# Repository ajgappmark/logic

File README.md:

# logic
Programmable logic probe

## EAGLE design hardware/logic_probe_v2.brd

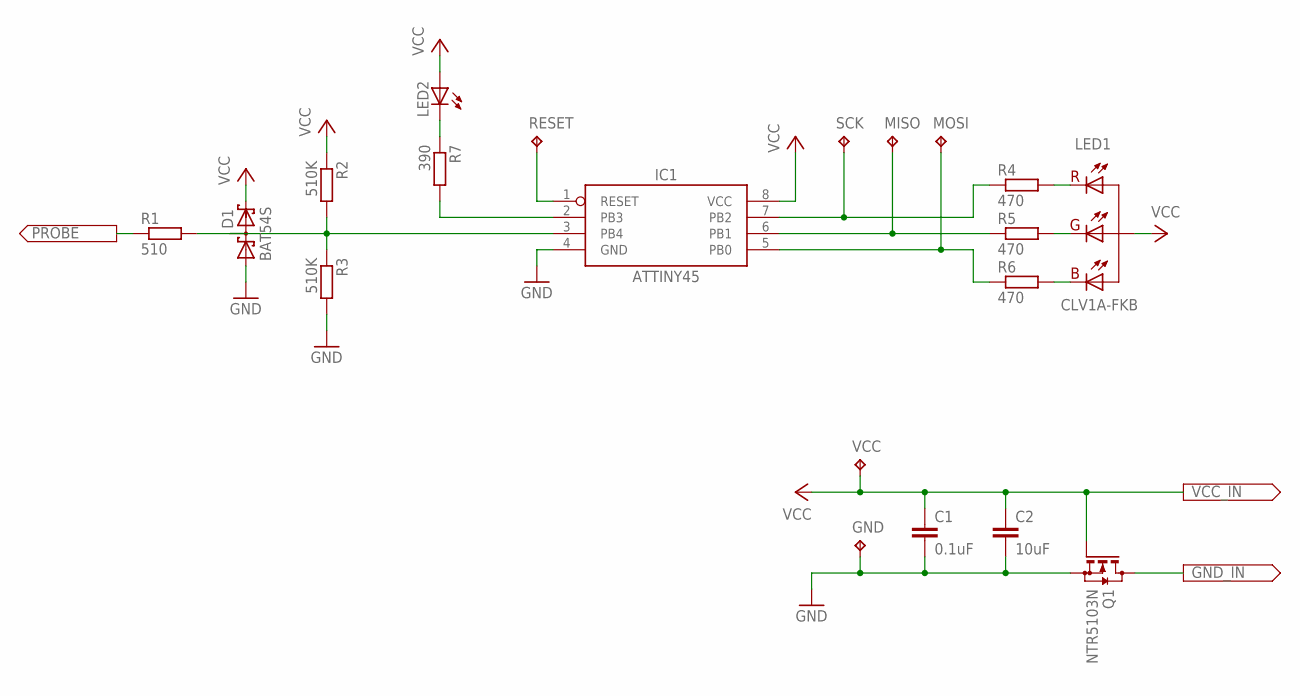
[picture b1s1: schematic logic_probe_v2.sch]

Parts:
C1: 0.1uF; C0805
C2: 10uF; C0805
D1: BAT54S; SOT23
GND: TPB1,27; B1,27
IC1: ATTINY45; TSSOP8
LED1: CLV1A-FKB; PLCC-4
LED2: LEDCHIPLED_0805; CHIPLED_0805
MISO: TPB1,27; B1,27
MOSI: TPB1,27; B1,27
Q1: NTR5103N; SOT23
R1: 510; R0805
R2, R3: 510K; R0805
R4, R5, R6: 470; R0805
R7: 390; R0805
RESET: TPB1,27; B1,27
SCK: TPB1,27; B1,27
VCC: TPB1,27; B1,27

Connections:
GND: C1.2, C2.2, D1.1 (A1), GND.TP, IC1.4 (GND), Q1.2 (S), R3.2
GND_IN: Q1.3 (D)
unnamed: LED1.1 (R), R4.2
unnamed: LED1.3 (G), R5.2
unnamed: LED1.4 (B), R6.2
unnamed: IC1.7 (PB2), R4.1, SCK.TP
unnamed: IC1.6 (PB1), MISO.TP, R5.1
unnamed: IC1.5 (PB0), MOSI.TP, R6.1
unnamed: IC1.2 (PB3), R7.2
unnamed: LED2.C, R7.1
unnamed: IC1.1 (RESET), RESET.TP
PROBE: R1.1
VCC: C1.1, C2.1, D1.2 (C2), IC1.8 (VCC), LED1.2 (CA), LED2.A, Q1.1 (G), R2.1, VCC.TP
VIN: D1.3 (C1A2), IC1.3 (PB4), R1.2, R2.2, R3.1

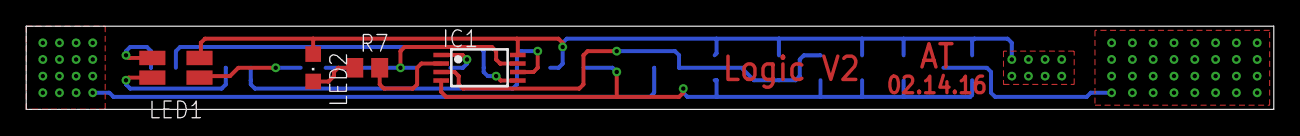
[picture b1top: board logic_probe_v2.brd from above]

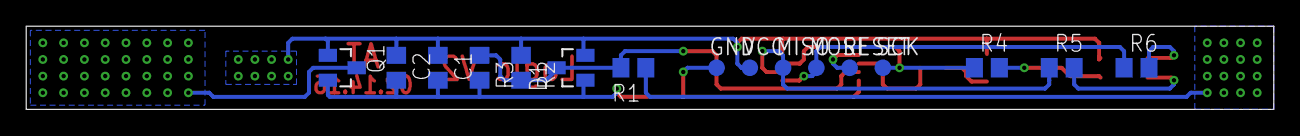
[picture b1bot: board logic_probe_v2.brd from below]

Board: 2 copper layers, 95.2 x 6.3 mm, 20 parts (16 on the bottom side), 12 nets.

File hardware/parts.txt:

http://www.digikey.com/product-detail/en/ATTINY45-20XUR/ATTI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	- IC MCU 8BIT 4KB FLASH 8TSSOP
http://www.digikey.com/product-detail/en/NTR5103NT1G/NTR5103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		- MOSFET N-CH 60V 0.26A SOT23
http://www.digikey.com/product-detail/en/BAT54SWFILM/497-141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		- DIODE ARRAY SCHOTTKY 40V SOT323
http://www.digikey.com/product-detail/en/CL21F104ZBCNNNC/127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		- CAP CER 0.1UF 50V Y5V 0805
http://www.digikey.com/product-detail/en/CL21A106KQCLRNC/127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		- CAP CER 10UF 6.3V X5R 0805
http://www.digikey.com/product-detail/en/RMCF0805JT390R/RMCF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	- RES SMD 390 OHM 5% 1/8W 0805
http://www.digikey.com/product-detail/en/RMCF0805JT470R/RMCF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	- RES SMD 470 OHM 5% 1/8W 0805
http://www.digikey.com/product-detail/en/RMCF0805JT510R/RMCF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	- RES SMD 510 OHM 5% 1/8W 0805
http://www.digikey.com/product-detail/en/RMCF0805JT510K/RMCF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	- RES SMD 510K OHM 5% 1/8W 0805
http://www.digikey.com/product-detail/en/CLV1A-FKB-CJ1M1F1BB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 - LED RGB DIFFUSED 4PLCC SMD
http://www.digikey.com/product-detail/en/QBLP631-IW/1516-108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		- LED WHITE 0805 SMD

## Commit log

2016-02-29 Added hardware files
2016-02-29 Added schematic PDF
2016-02-29 Added firmware and tools
2016-02-29 Added DigiKey part number list
